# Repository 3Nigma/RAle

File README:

Autor: Victor ADASCALITEI
admin@tuscale.ro

Despre proiect :
RAle [Romanian - Ale] - este un proiect menit sa-i invete pe prichindei si in general pe persoane interesate de microcontrolere arta acestor minunate creierase. Acest lucru este posibil avand la dispozitie placuta de teste Ale, pachetul RAle precum si carticica de invatare

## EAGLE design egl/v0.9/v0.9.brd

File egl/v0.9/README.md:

## A first look ##
The PEA board (known as _pAle_) is a 10x10cm, single-sided (with a few vias), PCB that has the following, internal, modular composition:
<center></center>

## Now that you are curious ##
From all the files listed in this folder, only 2 are very important for PEA. I'm talking here about:
* **v0.9.sch** which represents the schematic circuit itself
* **v0.9.brd** which reflects the physical layout of the components themselves

Both files (*sch* and *brd*) can be opened with the [Eagle Electrical CAD](http://www.cadsoftusa.com/) application which also has a *free version* available. These files represent the logical and physical construction specs for the _pAle_ board (version 0.9).

Let's go further and highlight some of the board's features.

### pAle's capabilities ###
* Built around the [USBTinyISP version 2.0](http://www.ladyada.net/make/usbtinyisp/) programmer, allowing the dumping of applications to Ale's little microcontroller
* Thanks to the programmer, the board does not require an external power supply and uses a modern data interface
* Is designed to work mainly with microcontrollers of type **Attiny[13|25|45|85]**. The original board uses an *Attiny25*, but it can also utilize other variants with little-or-no functional penalties. One such functional issue might be the internal temperature sensor which only the Attiny25 has. Under these circumstances, moving to a different microcontroller, this makes the book section devoted to this subject inapplicable
* It has a reset button which, as its name implies, resets the application that is currently running on the board
* Has a light-sensitive element through which one can read the level of lightning
* It has 8 general purpose LEDs, available to user applications
* It has 8 keys through which values from the environment can be sent to the user programs
* The chosen microcontroller family -*Attiny*- has many internal modules that can be used to develop complex projects

## The BOM list ##
Just to get a better understanding of the expenses involved in building the board, I give you the following *Bill Of Materials* table. The data was generated using Eagle's **bom.ulp** script.  
Therefore, as of this writing (version 0.9), the board required the following parts:

| Qty | Value      | Package      | Parts                                        |
| --- | ---------- | ------------ | -------------------------------------------- |
| 2   | 1.5k       | 0207/10      | R3, R8                                       |  
| 1   | 1.5k       | 0207/12      | R9                                           |
| 1   | 100nF      | C050-025X075 | C6                                           |
| 1   | 100u/25V   | E2,5-6       | C1                                           |  
| 3   | 10k        | 0204/7       | R7, R22, R23                                 |
| 7   | 10k        | 0207/10      | R6, R20, R21, R24, R25, R26, R27             |
| 1   | 10k        | 0207/15      | R11                                          |
| 1   | 12Mhz      | CSTLS_X      | X1                                           |
| 1   | 1k         | 0204/5       | R2                                           |
| 9   | 1k         | 0207/10      | R1, R12, R13, R14, R15, R16, R17, R18, R19   |
| 1   | 33         | 0207/10      | R5                                           |
| 1   | 33         | 0207/12      | R4                                           |
| 2   | 3v3        | ZDIO-7.5     | DZ1, DZ2                                     |
| 1   | 74164N     | DIL14        | V1                                           |
| 1   | 74165N     | DIL16        | V2                                           |
| 1   | 74HC125N   | DIL14        | IC1                                          |
| 1   | ATTINY2313 | DIL20        | IC3                                          |
| 1   | D1160_12   | D11XX        | FR35/1M                                      |
| 1   | Red        | LED3MM       | LED1                                         |
| 9   | TACT-64N   | B3F-10XX     | D0, D1, D2, D3, D4, D5, D6, D7, S1           |
| 1   | TINY25     |  DIL08       | IC2                                          |
| 1   | USBB-G     | PN61729      | X2                                           |
| 9   | Green      | LED3MM       | LED2, Q0, Q1, Q2, Q3, Q4, Q5, Q6, Q7         |

Please keep in mind the fact that if you plan to build the board yourself and you do have the know-how, the tools and the parts required, you will also need an Attiny2313 programmer to configure pAle's programmer module.

## What about the License? ##
Nothig to worry about! I just issued the board under the [Open Source Hardware (OSHA) License](http://www.oshwa.org/definition/) which means that you are free to hack it in any way you desire. Of course, I would very much appreciate to hear about your modifications.

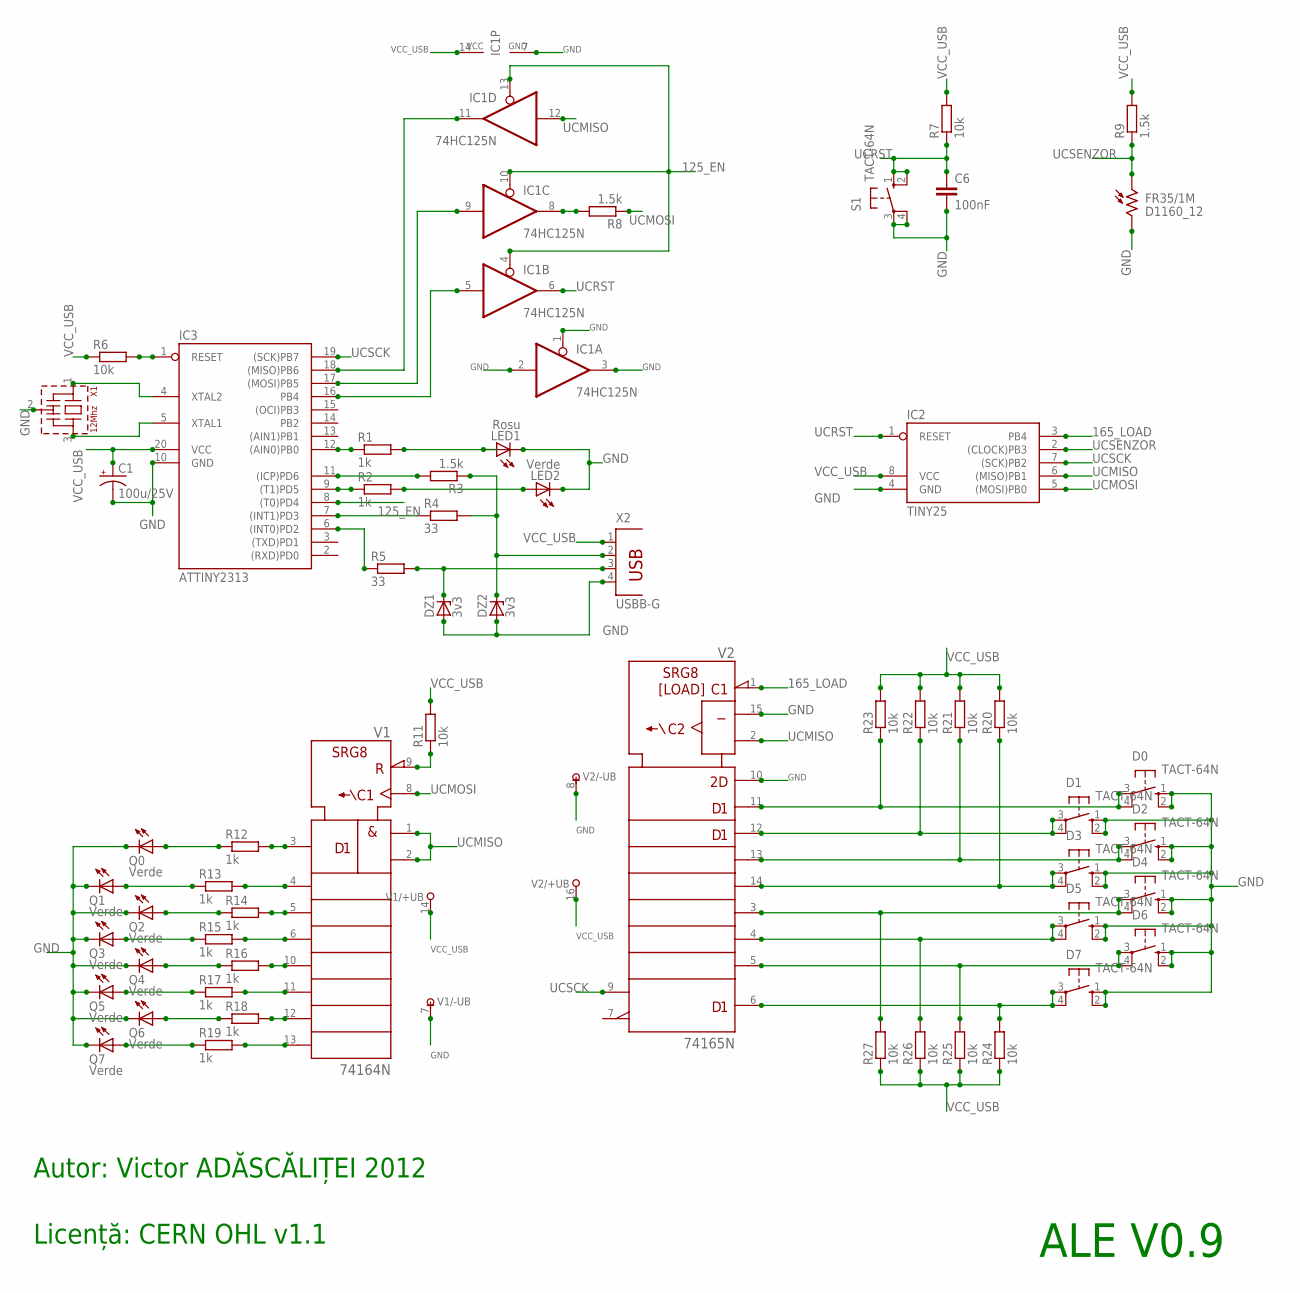
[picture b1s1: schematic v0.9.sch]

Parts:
C1: 100u/25V; E2,5-6
C6: 100nF; C050-025X075
D0, D1, D2, D3, D4, D5, D6, D7: TACT-64N; B3F-10XX
DZ1, DZ2: 3v3; ZDIO-7.5
FR35/1M: D1160_12; D11XX
IC1: 74HC125N; DIL14
IC2: TINY25; DIL08
IC3: ATTINY2313; DIL20
LED1: Rosu; LED3MM
LED2: Verde; LED3MM
Q0, Q1, Q2, Q3, Q4, Q5, Q6, Q7: Verde; LED3MM
R1, R12, R13, R14, R15, R16, R17, R18, R19: 1k; 0207/10
R2: 1k; 0204/5
R3, R8: 1.5k; 0207/10
R4: 33; 0207/12
R5: 33; 0207/10
R6, R20, R21, R24, R25, R26, R27: 10k; 0207/10
R7, R22, R23: 10k; 0204/7
R9: 1.5k; 0207/12
R11: 10k; 0207/15
S1: TACT-64N; B3F-10XX
V1: 74164N; DIL14
V2: 74165N; DIL16
X1: 12Mhz; CSTLS_X
X2: USBB-G; PN61729

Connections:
125_EN: IC1.4 (OE), IC1.10 (OE), IC1.13 (OE), IC3.8 ((T0)PD4)
165_LOAD: IC2.3 (PB4), V2.1 (SH/!LD)
GND: C1.-, C6.2, D0.1 (S), D0.2 (S1), D1.1 (S), D1.2 (S1), D2.1 (S), D2.2 (S1), D3.1 (S), D3.2 (S1), D4.1 (S), D4.2 (S1), D5.1 (S), D5.2 (S1), D6.1 (S), D6.2 (S1), D7.1 (S), D7.2 (S1), DZ1.A, DZ2.A, FR35/1M.2, IC1.1 (OE), IC1.2 (I), IC1.3 (O), IC1.7 (GND), IC2.4 (GND), IC3.10 (GND), LED1.K (C), LED2.K (C), Q0.K (C), Q1.K (C), Q2.K (C), Q3.K (C), Q4.K (C), Q5.K (C), Q6.K (C), Q7.K (C), S1.3, S1.4 (P1), V1.7 (-UB), V2.8 (-UB), V2.10 (SER), V2.15 (CLK_INH), X1.2 (VSS), X2.4
unnamed: IC1.5 (I), IC3.16 (PB4)
unnamed: IC1.9 (I), IC3.17 ((MOSI)PB5)
unnamed: IC1.8 (O), R8.2
unnamed: IC1.11 (O), IC3.18 ((MISO)PB6)
unnamed: R11.1, V1.9 (!CLR)
unnamed: IC3.1 (RESET), R6.2
unnamed: IC3.7 ((INT1)PD3), R4.1
unnamed: LED2.A, R2.2
unnamed: IC3.9 ((T1)PD5), R2.1
unnamed: D0.3, D0.4 (P1), R23.1, V2.11 (A)
unnamed: Q0.A, R12.1
unnamed: IC3.12 ((AIN0)PB0), R1.1
unnamed: LED1.A, R1.2
unnamed: IC3.6 ((INT0)PD2), R5.1
unnamed: IC3.11 ((ICP)PD6), R3.2
unnamed: DZ2.C, R3.1, R4.2, X2.2
unnamed: IC3.4 (XTAL2), X1.1
unnamed: DZ1.C, R5.2, X2.3
unnamed: IC3.5 (XTAL1), X1.3
unnamed: Q1.A, R13.1
unnamed: Q2.A, R14.1
unnamed: Q3.A, R15.1
unnamed: Q4.A, R16.1
unnamed: Q5.A, R17.1
unnamed: Q6.A, R18.1
unnamed: Q7.A, R19.1
unnamed: R12.2, V1.3 (QA)
unnamed: R13.2, V1.4 (QB)
unnamed: R14.2, V1.5 (QC)
unnamed: R15.2, V1.6 (QD)
unnamed: R16.2, V1.10 (QE)
unnamed: R17.2, V1.11 (QF)
unnamed: R18.2, V1.12 (QG)
unnamed: R19.2, V1.13 (QH)
unnamed: D1.3, D1.4 (P1), R22.1, V2.12 (B)
unnamed: D2.3, D2.4 (P1), R21.1, V2.13 (C)
unnamed: D3.3, D3.4 (P1), R20.1, V2.14 (D)
unnamed: D4.3, D4.4 (P1), R27.2, V2.3 (E)
unnamed: D5.3, D5.4 (P1), R26.2, V2.4 (F)
unnamed: D6.3, D6.4 (P1), R25.2, V2.5 (G)
unnamed: D7.3, D7.4 (P1), R24.2, V2.6 (H)
UCMISO: IC1.12 (I), IC2.6 ((MISO)PB1), V1.1 (A), V1.2 (B), V2.2 (CLK)
UCMOSI: IC2.5 ((MOSI)PB0), R8.1, V1.8 (CLK)
UCRST: C6.1, IC1.6 (O), IC2.1 (RESET), R7.1, S1.1 (S), S1.2 (S1)
UCSCK: IC2.7 ((SCK)PB2), IC3.19 ((SCK)PB7), V2.9 (QH)
UCSENZOR: FR35/1M.1, IC2.2 ((CLOCK)PB3), R9.1
VCC_USB: C1.+, IC1.14 (VCC), IC2.8 (VCC), IC3.20 (VCC), R6.1, R7.2, R9.2, R11.2, R20.2, R21.2, R22.2, R23.2, R24.1, R25.1, R26.1, R27.1, V1.14 (+UB), V2.16 (+UB), X2.1

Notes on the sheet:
ALE V0.9
Autor: Victor ADĂSCĂLIȚEI 2012
Licență: CERN OHL v1.1

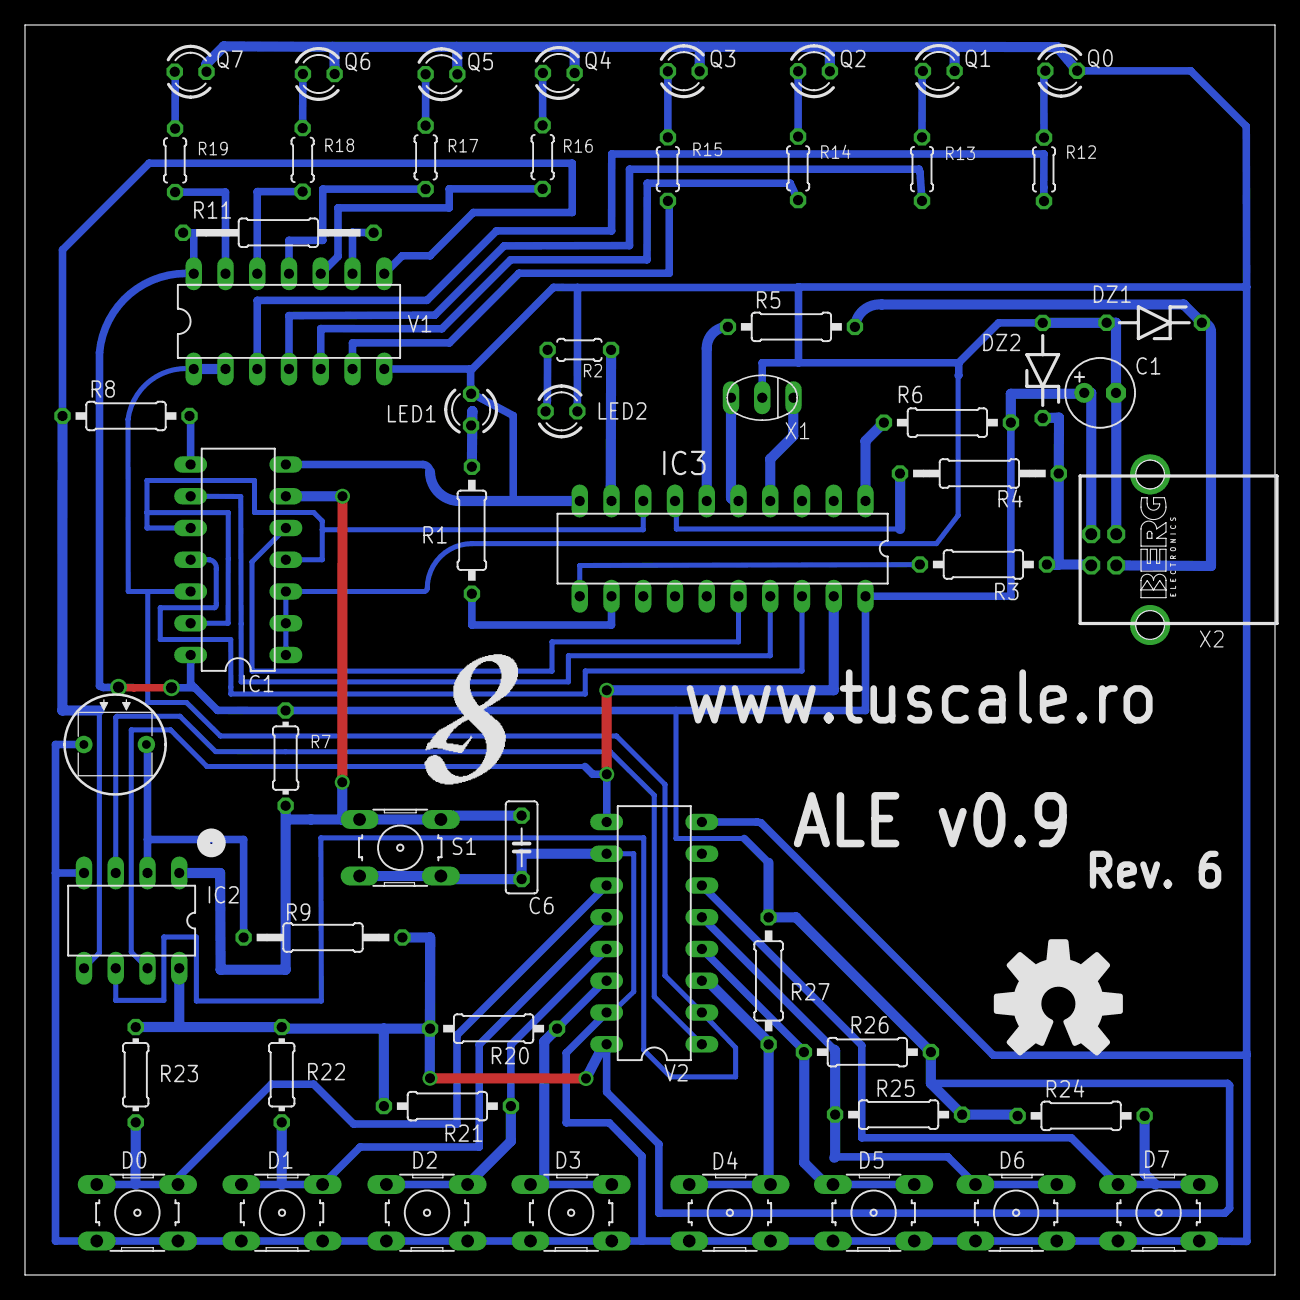
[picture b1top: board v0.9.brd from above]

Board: 2 copper layers, 100.0 x 100.0 mm, 57 parts (0 on the bottom side), 50 nets.

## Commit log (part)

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2012-06-03 First commit initializing the RAle repo.
2012-06-03 Added the rest of the comboboxes to the main form. Also, the application handles the request to exit button with a custom dialog in full native language. The main form is not resizable. Combobox exam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
2012-06-03 Modified the message a little bit and updated it to look more appealing.
2012-06-06 Added tooltips for the buttons in 'FereastraCod' and a simple click-handler for the 'Paraseste formular' button.
2012-07-09 Droped the 'Actualizeaza Exemple' button from info-form and rethought the download logic. Now, the download will take place automatically at program startup and different versions of the examples wil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
2012-07-10 Integrated the expand/colapse facility of code's form action group and made a structure that holds various needed aspectes from the code form.
2012-07-10 Tweaked the book examples combo-box. Now they do get loaded into the codeform. Edited the asm language file a little bit to better understand the syntax.
2012-07-10 This is the first working version fully compilable on windows (GTK+ 2.24, GtkSourceView 2.7.4). In this regards, the Makefile has a new rule ('win') that does this. Also, the make compilation was mad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
2012-07-11 Changed the expand/colapse code form icons and modified the focus response and profile of buttons from main, code and info form. Better aranged the buttons in the action region of the code form.
2012-07-12 Further removed unneeded programmers like avr910, mki variants and dragon variants.
2012-07-14 Removed Avr 32 bit MCU capability since 'usbtiny' doesn't support them and only one was ever configured in 'avrdude.conf' : 'AVR32UC3A0512'.
2012-07-15 Adapted the build files for the ACAD project (for naming principles) and updated the Readme file. The ChangeLog and NEWS files have also been reseted.
2012-07-22 Renamed 'surse' dir to 'src' as to make it more automake compatible.
2012-07-22 Started integrating the media files (images) into the sqlite database and made them available through the 'db_obtine_imagine_media_scalata' function. Also, the 'info form' now randomly loads a image 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
2012-07-25 Resolved bug #6 and issue #5. The TOC is functional through a well integrated button, but it's appearance is a subject of change.
2012-07-25 Added a simple frame to the book viewer resolving issue #10 in the process.
2012-08-01 Fixed the down-scrolling done at the last page that made it reset to the begining of the last page and eliminated the focus capability of the previous/next book button navigations. This brings a nice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
2012-08-15 Added license support for the hardware part.
2012-08-16 Added Ale v0.9 and USBTiny v2.0 board schematics/layout files. Both are done using Eagle Electric CAD software. Ale is distributed with the learning packet while the USBTiny files were added for futu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
2012-08-17 Added a formatted README file in 'eagle/v0.9', replaced the header image of 'eagle/usbtiny/README.md' and centered all the othe README's images with a 'center' tag.
2012-08-19 Modified 'README.md' to correctly point to the board schematic/layout. Previous commit had a broken url.
2012-08-25 Restructured the 'doc/README.md' a little bit and updated the LibreOffice link to point to a Romanian version.
2012-09-09 Worked on the book on section 'Un pic de istorie...' integrating Ale's review observations and extending the text a little bit.
2012-09-17 Update src/dafus/usb.h
    Done mostly formating edits. Be advised that since the browser was used to make these edits, they weren't tested!
2012-10-05 [work on eagle] Made the board a perfect fit in a 100x100mm square and made it ready for manufacturer production by grouping objects in appropriate layers.
2012-10-13 [book work] corected the 'Parity-Check-Algorithm' and explained it a little bit. Reviewed until example 4s.
2012-10-14 [book work] Reviewed section 4.1s and applied Alexandra's comments.
2012-10-15 [book work] Reviewed section 6s according to Alexandra's observations.
2012-10-15 [book work] Reviewed example 9s.
2012-10-16 [book work] Reviewed examples 12s and 12.1s + added a osci' capture in 12s.
2012-10-16 [book work] Reviewed example 16s.
2012-10-21 [book work] Tweaked the formatting a little bit (missed some tables).
2012-10-21 [psale] Modified app to take account of the new structure of the examples table. With the new modifications come the posibility of ordering the shown-examples list with the aid of the 'OrdineAfis' co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
2012-10-25 [psale work] Added 'OCR1C' keyword to asm language keyword definitions.
2012-10-27 [psale src] Added the 'Salveaza lucrul' functionality as well as small code-changed tracker.
2012-10-29 [psale work] Added functionality to the EEPROM action form. The buttons work and also does the edditing. There's a small problem with the tooltip, but hopefully it will be resolved shortly.
2012-10-31 [psale work] Added tooltips and shortcut keys to the EEPROM form button section.
2012-11-03 [psale work] Implemented 'Încarcă pe Ale' on win7
    Added a new module called 'os' that gathers various operating system
    specific actions. This was done to satisfy win's lack of executing and
    redirecting console apps by api calls.
    Refactored the 'fcod:btIncarcaPeAle_click' function.
2012-11-03 [psale work] Added 'c' language switching
    The user is now able to toggle the examples list from ASM ('s')~ default
    ~ to C ('c') by pressing Ctrl+S on the main form. The database does not
    contain 'c' examples yet but that will be fixed next. Also, the 'fprin'
    module got a structure (called 'FormularPrincipal') to bring it inline
    with the other form entities and make the processing a little bit more
    uniform.
2012-11-04 [psale work] Added planets icons (used in the info. form) under version control
2012-11-04 [psale work] Added COPYING notice to the new folder structures.
2012-11-05 [psale work] Ported updater to win
    All seams to be working ...
2012-11-05 [psale work] Added a new 'fl' (file link) module that takes the burdain of file system interactions. Currently, it handles the media (images) of the app thus freeing the DB from this burdain and help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
2012-11-05 [psale work] Added SSL options to updater
    ... making the windows distribution fully capable of working with gist's
    HTTPS. (tested!) The certificates used come from the CURL site and are
    called "cacert.pem".
2012-11-07 [psale work] Added 'Actualizează' button in 'finfo' form. No logic has been atached yet, only the infrastructure (callback, tooltip and shortcut-keys) was layed out. Refactored the 'finfo' button cre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
2012-11-07 [psale work] Completed the 'psale:finfo:Actualizeaza' button-clicked code reporting better messages and refactoring the code a little bit. Also, a structure that holds a update record has been added 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
2012-11-08 [book work] Added info about '.include's in section 'O alternativă la ceea ce știm ...' to reduce code size.
2012-11-09 [psale work] Added support for form icons. Used it in 'fprin'. The image isn't choosen yet so it's not available I'm afraid but it will come shortly.
2012-11-10 [psale work] Went to a relative app path calling
    Since the installer will gurantee that the needed binaries (avr-gcc,
    avrdude, etc.) will be in the PATH, there is no need for an absolute
    binary path invocation so the 'al' and 'fcod' modules were updated in
    this regards.
2012-11-12 [psale work] Renamed license file
    to make it more clearer about it's content.
2012-11-12 [psale work] Updated Makefiles
    and fixed installer shortcuts creation bug. The Makefiles were updated
    to better clean the 'construit/CD/pachete' directory. 'compilator.zip'
    creation capability was also added.
2012-11-12 [psale work] Added pre-driver-install MsgBox
    And also updated the section sizes.
2012-11-15 [psale work] Added the rest of available C equivalent codes from the old RAle project.
2012-11-15 [psale work] Added check and upgrade local rpsale from psale:main.
2012-11-16 [book work] Added answer support for the answers themselv to estimate the total pagecount of the book.
2012-11-17 [book work] Added answers in apendix for sections 11s:13s.
2012-11-17 [psale work] Cleaned examples 14s and 15s.
2012-11-23 [book work] The answers section seems to be complete. Also, a few review observations were applied.
2012-11-25 [psale work] Added a first version of a CD label to the psAle CD. It uses gLabels and is intended for the SIGMA DPC-11-2615 2CD/A4 labels paper.
2012-12-07 [book work] Skimed over the entire content and aligned it, making it ready for printing.
2012-12-15 [book work] Added a first erata document holder used for tracking changes between book releases (version changes).
2012-12-21 [psale work] Refactored the 'os' renaming some functions.
2012-12-22 [psale work] Made the 'sd' module also hold basic-often-used algos. In this regards, it was renamed to 'sda' wih the letter 'a' denoting just that.A first string to Versiune parsing method was create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
2012-12-28 [psale work] Version data is now returned in heap from database and the sql statements got all the same case-size.
2012-12-28 [psale work] Handled "afiseaza" action type required by console invocation of 'rpsale'.
2012-12-28 [rpsale work] Cleaned up the '#include' region.
2012-12-28 [rpsale work] Added a more friendly message for unknown arguments passed at program startup.
2012-12-29 [psale work] Updated 'os_obtine_versiune_server' to work with 'rpsale' and 'os_executa_comanda_si_obtine_rezultat' to allow further invocations and collecting of console output while in linux.
2012-12-29 [psale work] Fixed memory deallocation glitch.
2012-12-29 [psale work] Cleaned up 'Actualizează' button from 'finfo' since it is not needed anymore.
2012-12-30 [psale] Am adăugat legătură la imaginea resursă folosită de finfo atunci când nu s-a găsit nici-o versiune nouă. Acum există 2 astfel de imagini : una când s-a găsit o actualizare disponibilă și una 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
2012-12-31 [psale] Formularul de informații arată acum și descrierea versiunilor așa cum apar ele în tabelul 'modificari'. Acestea sunt afișate într-o regiune special marcată. Baza de date, de asemenea, s-a act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
2013-01-04 [psale] S-au netezit cutele de cod linux->win32
    > Makefile-ul din rădăcină nu mai construiește PDF-ul pentru 'win',
    acesta se construiește doar pentru 'linux', o țintă proaspăt adăugată.
    > Inițializarea modulului 'db' a fost completată pentru a urmări
    existența bazei de date. În caz contrar, o eroare este emisă, iar
    inițializarea este considerată un eșec. (Versiunea precedentă nu realiza
    acest lucru!)
2013-01-04 [psale] Am integrat actualizatorul cu principalul
    ... în windows! Se pare că ambele comunică bine. Urmează să se realzieze
    teste. De asemenea, o serie de macro-uri au fost mutate în modulu 'sda'.
2013-01-05 [cărțulie] S-a implementat erata 1.0->1.1, mai se așteptă actualizarea imaginii cu 'finfo' cu actualizările din împrejurimi și se poate spune că s-a trecut la versiunea 1.1 a cărțuliei.
2013-01-06 [cărțulie] Sa restructurat directorul de imagini ('img') în subdirectoare sugestive. S-au importat legăturile imaginilor web ale cărțuliei local pentru a evita cazul în care o astfel de resursă nu ma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
2013-01-06 [psale] Am completat secvența de apel realizată pe avrdude în momentul citirii memoriei EEPROM pentru a proteja calea aplicației invocate de spații. În linux, fluxul de eroare s-a aruncat spre /dev/n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
2013-01-08 [psale] Am defalcat nucleul aplicatiei de dependente
    Pentru a putea fragmenta pachetele si a nu suprasolicita serviciul de
    gazduire. De asemenea, formularului de actualizare ('factualizare' din
    reinoitor) i s-a resetat secventa de declansare din starea de descarcare
    a pachetului actualizant si a aplicarii sale cu succes. Se impune o
    astfel de decizie de moment ce retelele pot fi supuse la latente
    variabile.
2013-01-14 [psale] S-a curatat un pic scriptul aducator de instructiuni
    parazite non-windows.
2013-03-28 [psale] S-a rezolvat observația #22. Acum fișierele fără denumire primesc, la salvare, extensie implicită.
2013-04-01 [psale] Rezolvat goanga #25
    care făcea referire la distribuția de windows : bic-ul nu se afișa
    atunci când era necesar în fcod, iar codul nu era împiedicat să ajungă
    pe creieraș. Astfel, starea flash-ului devenea invalidă după o
    operațiune eșuată de scriere a sa.
2014-03-03 Update README.md
    Translated and updated the content to English.
2014-03-04 Update README.md
    Updated and internationalized the content of this README.
